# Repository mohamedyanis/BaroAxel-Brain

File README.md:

# BaroAxel Brain

This Printed Circuit Board (PCB) is based on the STM32 microcontroller as well as MEMS sensors (MPU6050 and BMP280).
The PCB is designed using the free and open source software <a href="https://github.com/KiCad">KiCad</a>. 

## More Details
BaroAxel Brain is a compact Printed Circuit Board (PCB) designed for industrial instrumentation applications. It integrates the STM32L0 series microcontroller, MPU6050 accelerometer, and BMP280 barometer, providing a comprehensive solution for asynchronous motor anomaly detection and other MEMS-based applications.

This board operates with a wide input voltage range from 4.75V to 12V, ensuring compatibility with various power sources commonly found in industrial environments. It features multiple connectors for UART communication, analog-to-digital conversion, and timer functions, offering flexibility for interfacing with diverse sensors and peripherals.

The STM32L0 MCU, renowned for its low-power operation and high-performance computing capabilities, drives the board's functionality. The integrated MPU6050 accelerometer enables precise measurement of acceleration, essential for monitoring vibrations and detecting anomalies in industrial machinery. Additionally, the BMP280 barometer facilitates accurate measurement of atmospheric pressure, enabling environmental monitoring in diverse industrial settings.

The compact design of BaroAxel Brain optimizes space utilization, making it suitable for integration into space-constrained industrial systems while maximizing functionality. It also includes an SWD connector for firmware updates, ensuring easy maintenance and scalability of the board.

This combination of features makes BaroAxel Brain an ideal choice for applications requiring robust industrial instrumentation, such as asynchronous motor anomaly detection and drone instrumentation, among others.

This board is designed back to 2021, ordered in 2023, and hand soldered in April 2024<br><br>

## Features :dart:
* [x] Four layers PCB
* [x] Low power
* [x] Small size (50x50mm)
* [x] Very easy to use

## Thank _You_!
Please :star: this repo to help us improve the quality.
<br><br>

## PCB Block Diagram
PCB System Block
:---------------------:

## 3D Viewer
Front View           | Back View
:---------------------:|:------------------:
 | 
Side View 1         |  Side View 2
 | 
Side View 3         |  Side View 4
 | 

## Before, During and After Soldering
Before 1            | Before 2
:---------------------:|:------------------:
 | 
During 1         |  During 2
 | 
After 1         |  After 2
 | 

## Testing the Functionality
Here I tested the functionality of the board after assembling it. I tested the built-in LEDs and the IMU (MPU6050) using I2C protocol, and print some texts on the laptop's screen using putty application via the UART-TTL converter.<br><br>

## 3D Enclosure Design
Here is the 3D Enclosure I designed using SolidWorks. The design contains the top and bottom pieces as well as a small glass plate just to show the electronics inside. Of course assembled with SolidWorks Assembly.
See the folder [3D](3D) in order to get the designs and print the parts using a 3D Printer.<br><br>
Enclosure Top           | Enclosure Bottom
:---------------------:|:------------------:
 | 
Enclosure Side 1         |  Enclosure Side 2
 | 

## Requirements

If you want to review the PCB or yoou wanna edit the schematics/layout, yoou only need to install KiCad software to your machine.

* Go to the <a href="https://www.kicad.org/download/">Official KiCad Download Page</a>.
* Select your operating system.
* Download the executable file and install it.

## Documentations
Open the [Datasheets](Datasheets) folder and you will find all the datasheets, applications notes, and design guidelines that help you understand the design better.

## How To Use It

1. Install this repository, click <a href="https://github.com/mohamedyanis/BaroAxel-Brain/archive/master.zip"> here </a> to install it. Or use git command:
```bach
git clone https://github.com/mohamedyanis/BaroAxel-Brain.git
```
3. Extract the folder and open it.
4. Navigate for the [Manufacturing](Manufacturing) folder.
5. Go to your best PCB manufacturer website and click on quote.
6. Upload the [BaroAxel_Brain_Gerber.rar](Manufacturing/Gerber/BaroAxel_Brain_Gerber.zip) in order to order the board.

## License
The content of this project is licenced under the [BSD 3-Clause "New" or "Revised" License](LICENSE).

## Contributing 💡
If you want to contribute to this project and make it better with new ideas, your pull request is very welcomed.<br>
If you find any issue just put it in the repository issue section, thanks!<br><br>
.سبحَانَكَ اللَّهُمَّ وَبِحَمْدِكَ، أَشْهَدُ أَنْ لا إِلهَ إِلأَ انْتَ أَسْتَغْفِرُكَ وَأَتْوبُ إِلَيْكَ

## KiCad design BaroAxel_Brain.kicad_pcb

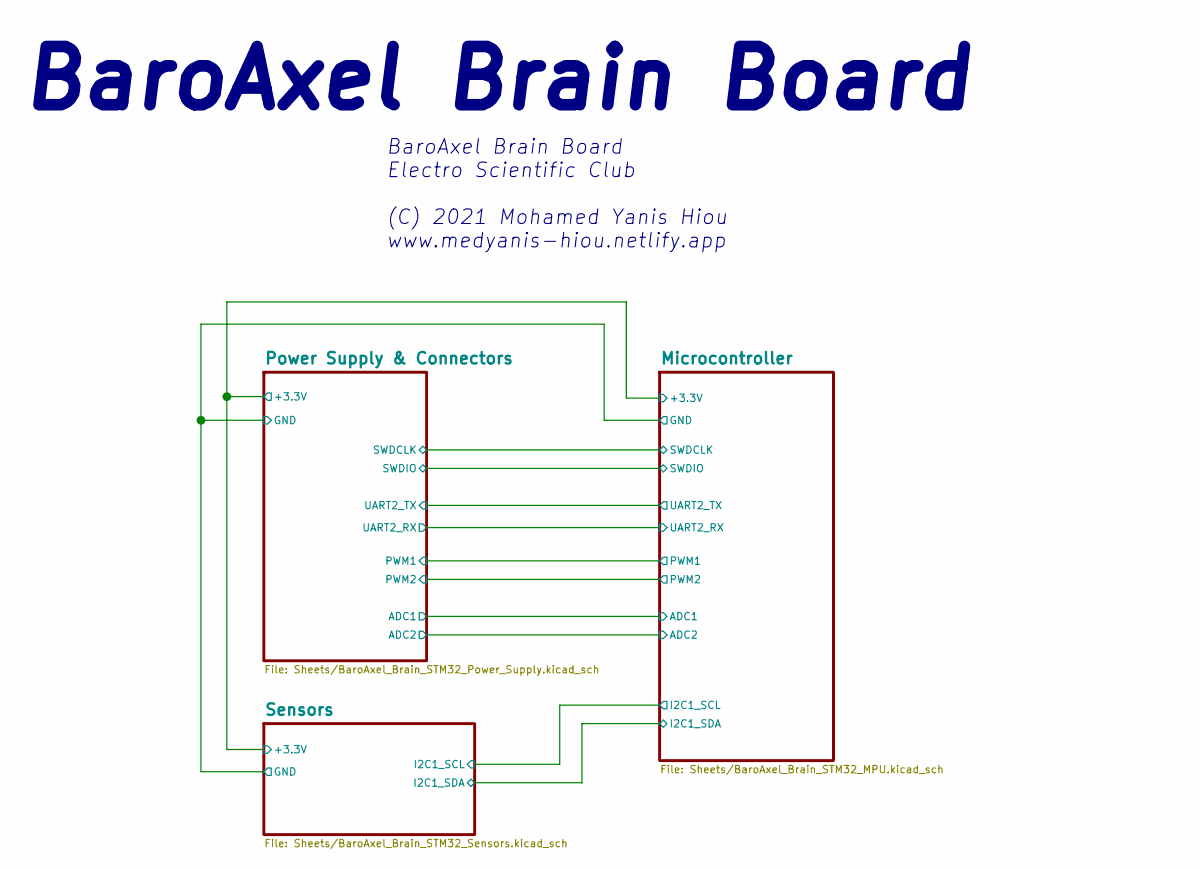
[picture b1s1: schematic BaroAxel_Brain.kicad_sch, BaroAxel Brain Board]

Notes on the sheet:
BaroAxel Brain Board Electro Scientific Club (C) 2021 Mohamed Yanis Hiou www.medyanis-hiou.netlify.app
BaroAxel Brain Board

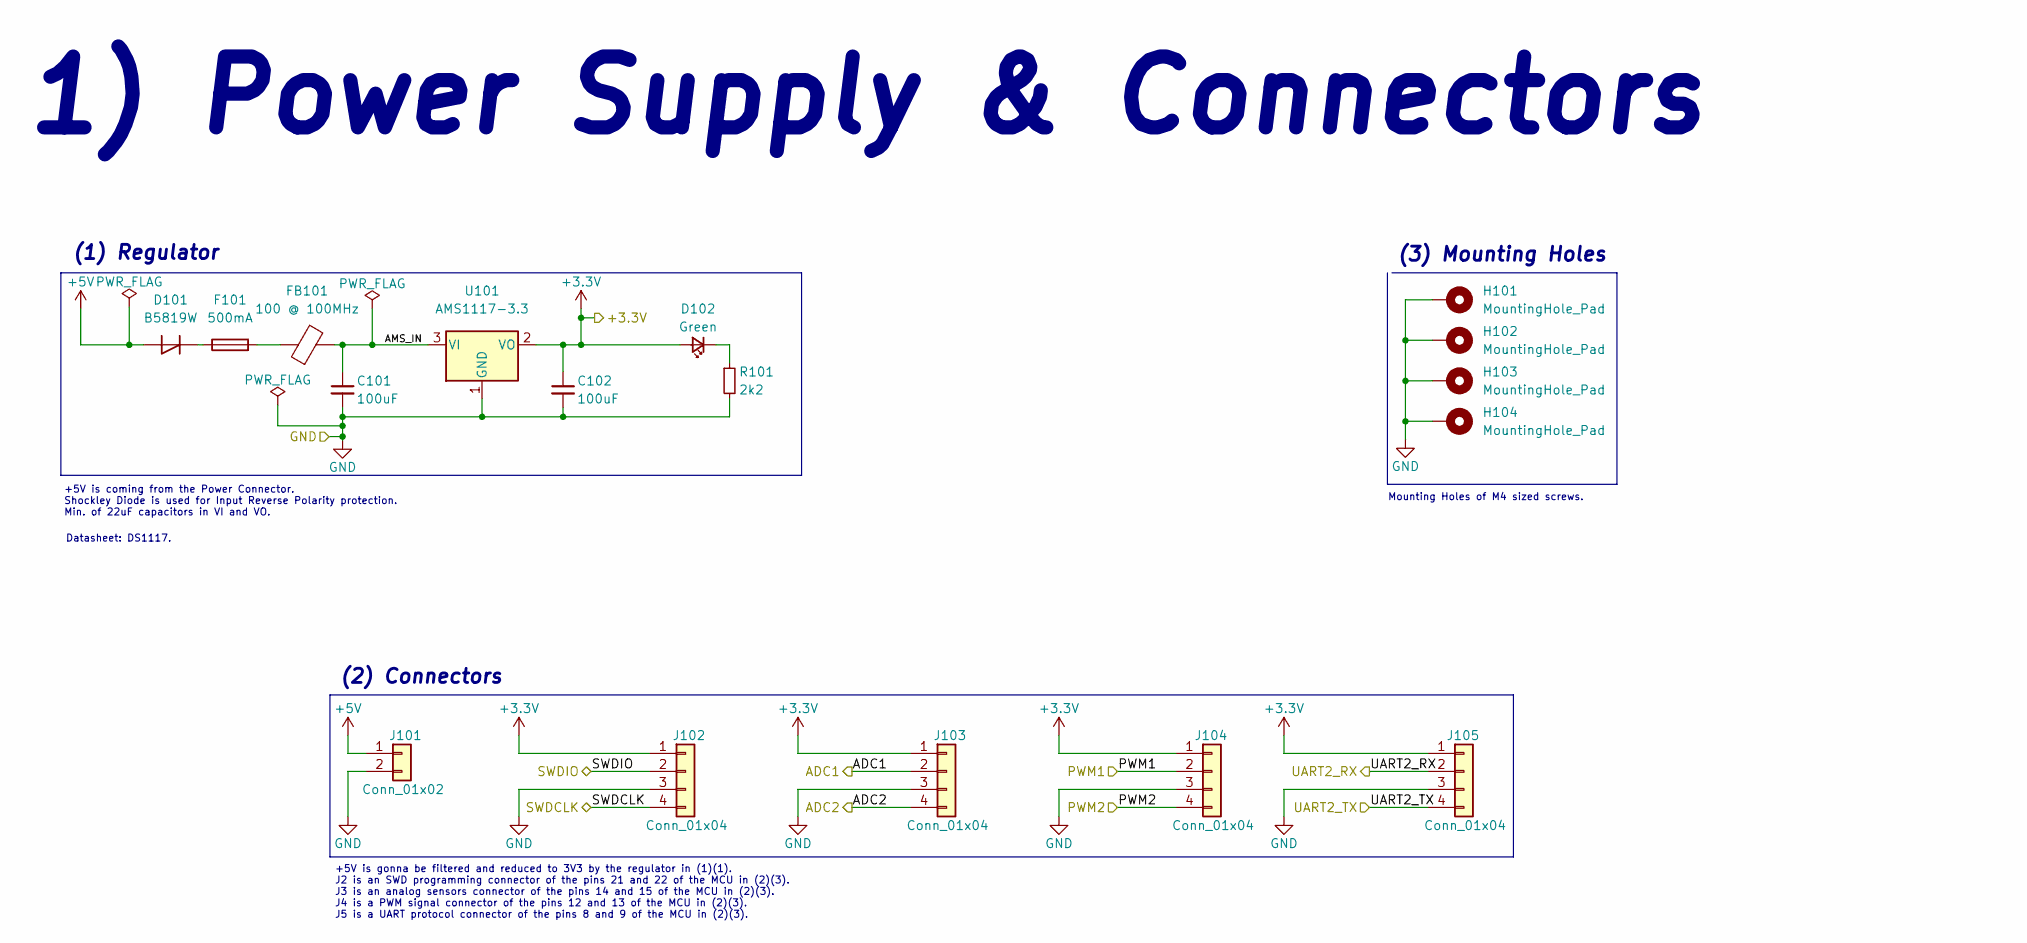
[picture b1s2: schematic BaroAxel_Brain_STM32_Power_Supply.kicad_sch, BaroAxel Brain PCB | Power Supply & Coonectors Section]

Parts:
C101, C102: 100uF; C_0603_1608Metric
D101: B5819W; D_1206_3216Metric
D102: Green; LED_0603_1608Metric
F101: 500mA; Fuse_0805_2012Metric
FB101: 100 @ 100MHz; L_0603_1608Metric
H101, H102, H103, H104: MountingHole_Pad; MountingHole_4.3mm_M4_Pad_Via
J101: Conn_01x02; JST_XH_S2B-XH-A_1x02_P2.50mm_Horizontal
J102, J103, J104, J105: Conn_01x04; JST_XH_S4B-XH-A_1x04_P2.50mm_Horizontal
R101: 2k2; R_0402_1005Metric
U101: AMS1117-3.3; SOT-223-3_TabPin2

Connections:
+5V: D101.2 (A), J101.1
/Microcontroller/ADC1: J103.2; also elsewhere on the board
/Microcontroller/ADC2: J103.4; also elsewhere on the board
/Microcontroller/PWM1: J104.2; also elsewhere on the board
/Microcontroller/PWM2: J104.4; also elsewhere on the board
/Microcontroller/SWDCLK: J102.4; also elsewhere on the board
/Microcontroller/SWDIO: J102.2; also elsewhere on the board
/Microcontroller/UART2_RX: J105.2; also elsewhere on the board
/Microcontroller/UART2_TX: J105.4; also elsewhere on the board
/Power Supply & Connectors/AMS_IN: C101.1, FB101.2, U101.3 (VI)
unnamed: D101.1 (K), F101.1
unnamed: D102.1 (K), R101.1
unnamed: F101.2, FB101.1

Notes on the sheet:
+5V is coming from the Power Connector. Shockley Diode is used for Input Reverse Polarity protection. Min. of 22uF capacitors in VI and VO.
1) Power Supply & Connectors
Datasheet: DS1117.
(3) Mounting Holes
Mounting Holes of M4 sized screws.
+5V is gonna be filtered and reduced to 3V3 by the regulator in (1)(1). J2 is an SWD programming connector of the pins 21 and 22 of the MCU in (2)(3). J3 is an analog sensors connector of the pins 14 and 15 of the MCU in (2)(3). J4 is a PWM signal connector of the pins 12 and 13 of the MCU in (2)(3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
(1) Regulator
(2) Connectors

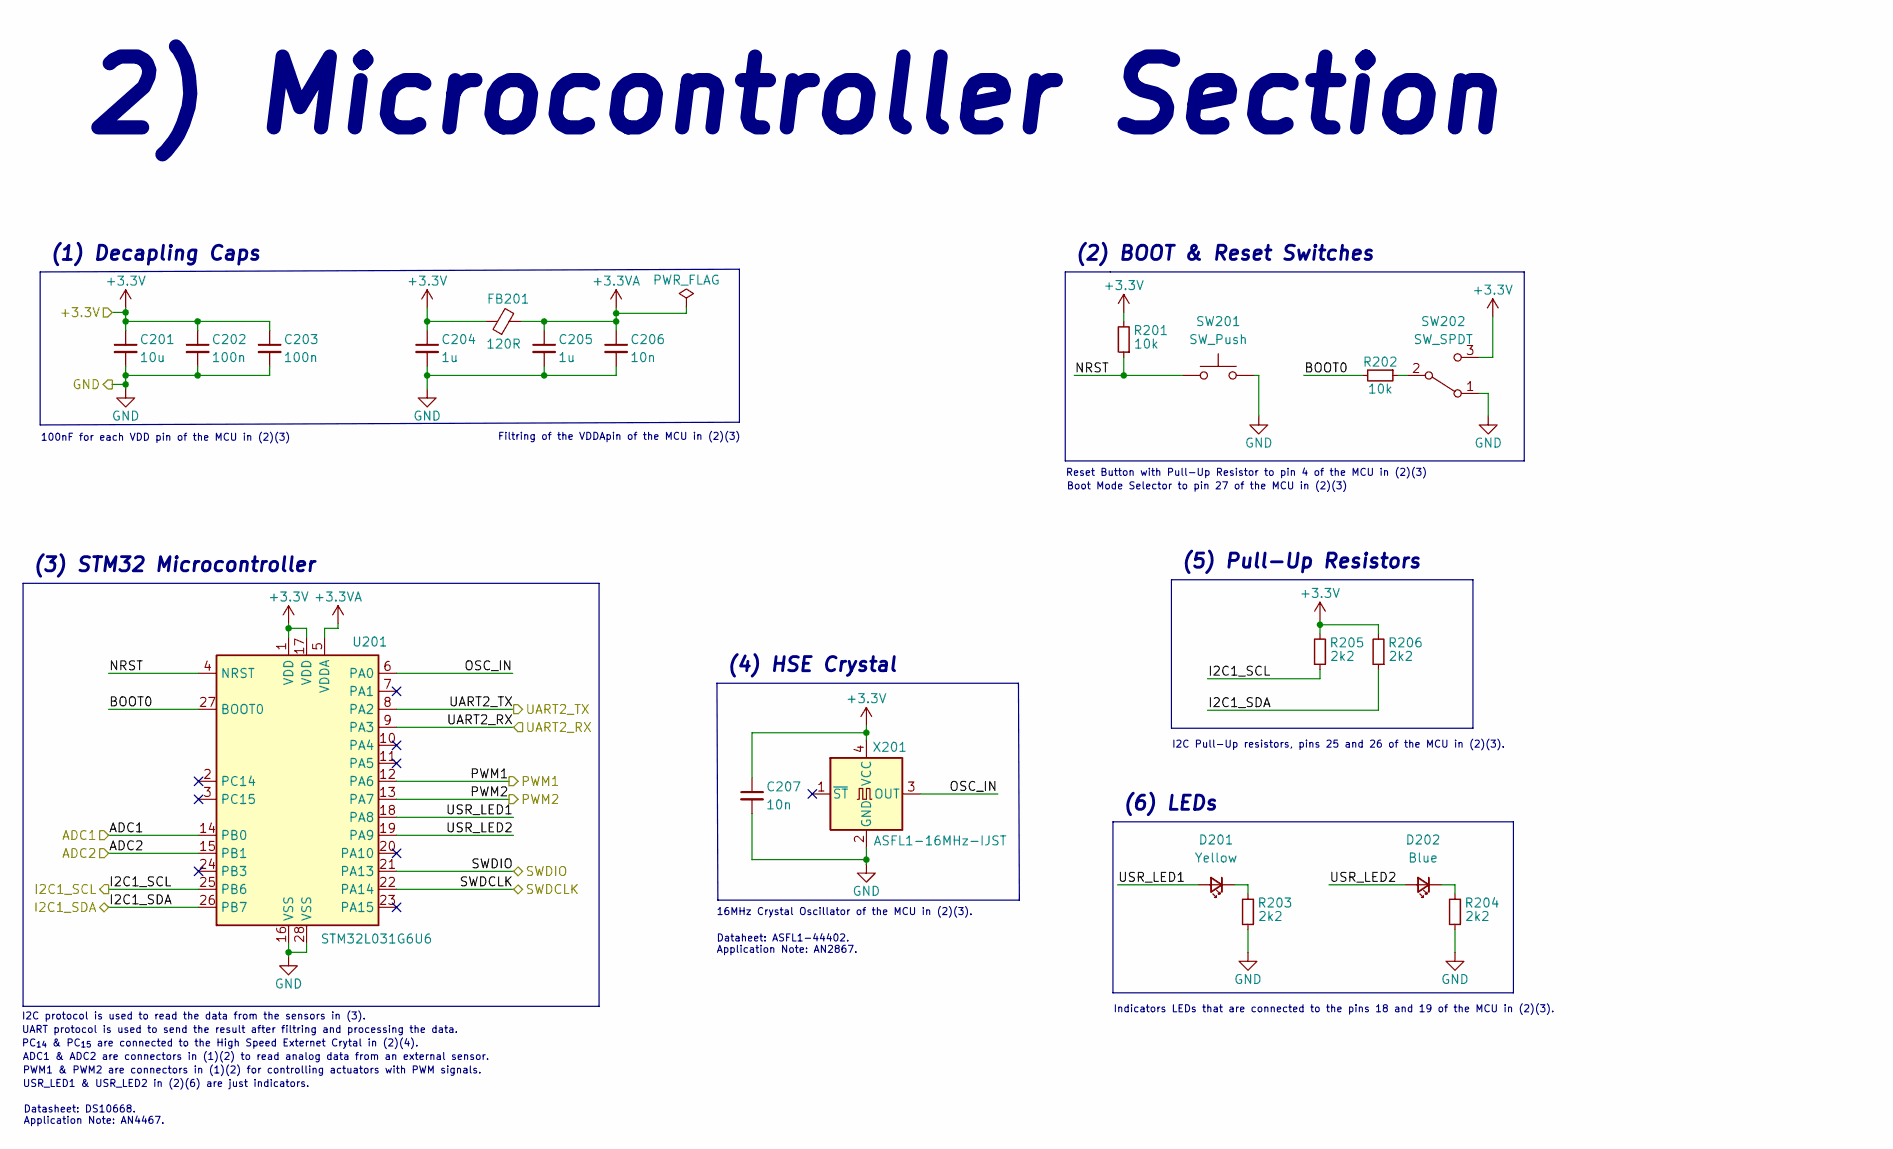
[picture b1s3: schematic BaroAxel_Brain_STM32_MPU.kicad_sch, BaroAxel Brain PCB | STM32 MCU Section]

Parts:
C201: 10u; C_0402_1005Metric
C202, C203: 100n; C_0402_1005Metric
C204, C205: 1u; C_0402_1005Metric
C206, C207: 10n; C_0402_1005Metric
D201: Yellow; LED_0603_1608Metric
D202: Blue; LED_0603_1608Metric
FB201: 120R; L_0603_1608Metric
R201, R202: 10k; R_0402_1005Metric
R203, R204, R205, R206: 2k2; R_0402_1005Metric
SW201: SW_Push; SW_SPST_B3U-1000P-B
SW202: SW_SPDT; SW_SPDT_PCM12
U201: STM32L031G6U6; QFN-28_4x4mm_P0.5mm
X201: ASFL1-16MHz-IJST; Oscillator_SMD_SeikoEpson_SG8002LB-4Pin_5.0x3.2mm

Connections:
+3.3VA: C205.1, C206.1, FB201.2, U201.5 (VDDA)
/Microcontroller/ADC1: U201.14 (PB0); also elsewhere on the board
/Microcontroller/ADC2: U201.15 (PB1); also elsewhere on the board
/Microcontroller/BOOT0: R202.2, U201.27 (BOOT0)
/Microcontroller/I2C1_SCL: R205.1, U201.25 (PB6); also elsewhere on the board
/Microcontroller/I2C1_SDA: R206.1, U201.26 (PB7); also elsewhere on the board
/Microcontroller/NRST: R201.1, SW201.1, U201.4 (NRST)
/Microcontroller/OSC_IN: U201.6 (PA0), X201.3 (OUT)
/Microcontroller/PWM1: U201.12 (PA6); also elsewhere on the board
/Microcontroller/PWM2: U201.13 (PA7); also elsewhere on the board
/Microcontroller/SWDCLK: U201.22 (PA14); also elsewhere on the board
/Microcontroller/SWDIO: U201.21 (PA13); also elsewhere on the board
/Microcontroller/UART2_RX: U201.9 (PA3); also elsewhere on the board
/Microcontroller/UART2_TX: U201.8 (PA2); also elsewhere on the board
/Microcontroller/USR_LED1: D201.2 (A), U201.18 (PA8)
/Microcontroller/USR_LED2: D202.2 (A), U201.19 (PA9)
unnamed: D201.1 (K), R203.2
unnamed: D202.1 (K), R204.2
unnamed: R202.1, SW202.2 (B)

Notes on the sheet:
I2C Pull-Up resistors, pins 25 and 26 of the MCU in (2)(3).
16MHz Crystal Oscillator of the MCU in (2)(3).
Boot Mode Selector to pin 27 of the MCU in (2)(3)
2) Microcontroller Section
USR_LED1 & USR_LED2 in (2)(6) are just indicators.
Datasheet: DS10668. Application Note: AN4467.
(4) HSE Crystal
UART protocol is used to send the result after filtring and processing the data.
100nF for each VDD pin of the MCU in (2)(3)
(1) Decapling Caps
ADC1 & ADC2 are connectors in (1)(2) to read analog data from an external sensor.
(5) Pull-Up Resistors
Indicators LEDs that are connected to the pins 18 and 19 of the MCU in (2)(3).
(6) LEDs
(2) BOOT & Reset Switches
PC_{14} & PC_{15} are connected to the High Speed Externet Crytal in (2)(4).
PWM1 & PWM2 are connectors in (1)(2) for controlling actuators with PWM signals.
(3) STM32 Microcontroller
I2C protocol is used to read the data from the sensors in (3).
Filtring of the VDDApin of the MCU in (2)(3)
Dataheet: ASFL1-44402. Application Note: AN2867.
Reset Button with Pull-Up Resistor to pin 4 of the MCU in (2)(3)

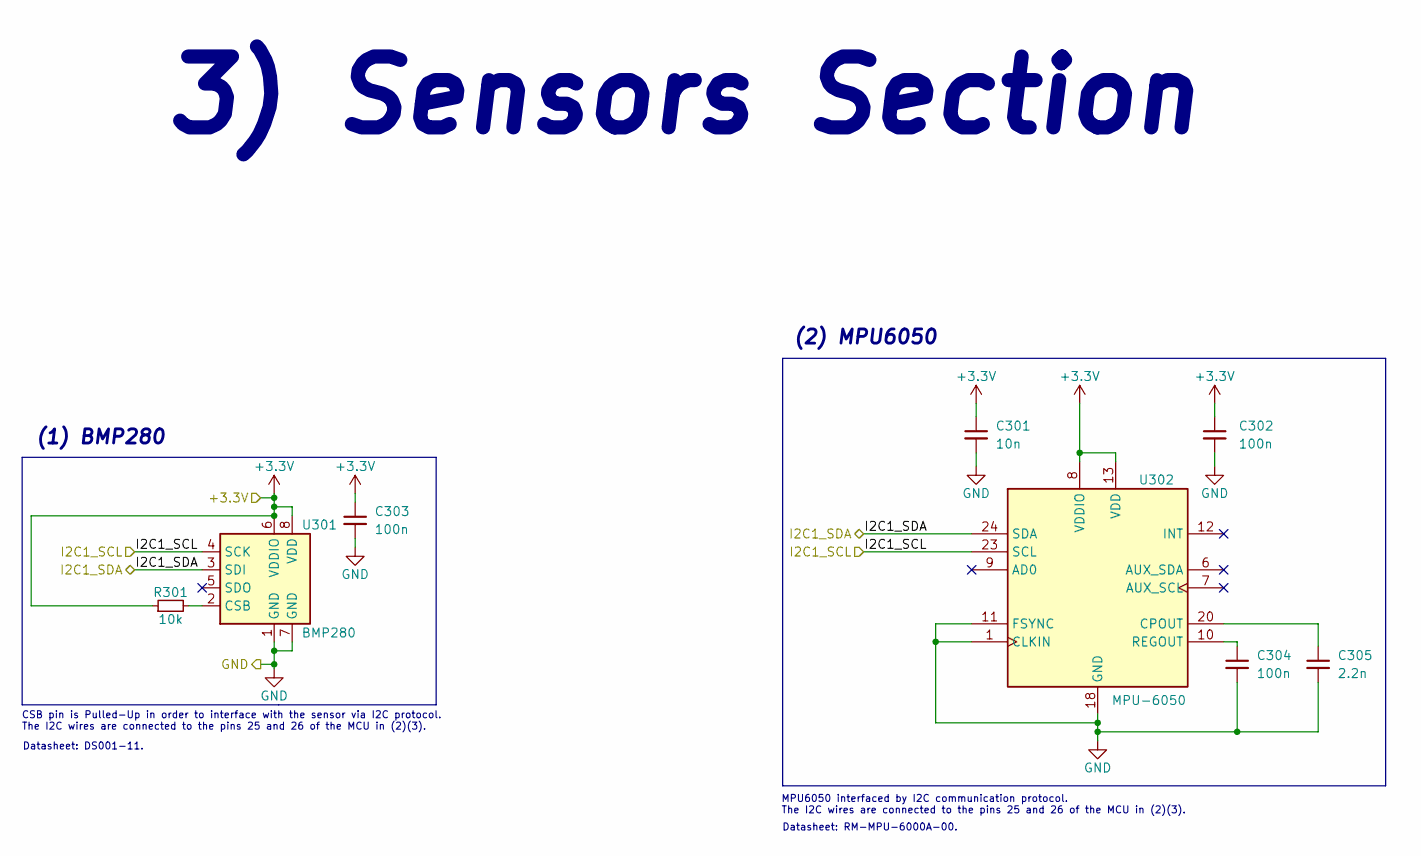
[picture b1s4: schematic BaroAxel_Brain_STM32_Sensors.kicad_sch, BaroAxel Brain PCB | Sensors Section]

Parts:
C301: 10n; C_0402_1005Metric
C302, C303, C304: 100n; C_0402_1005Metric
C305: 2.2n; C_0402_1005Metric
R301: 10k; R_0402_1005Metric
U301: BMP280; Bosch_LGA-8_2x2.5mm_P0.65mm_ClockwisePinNumbering
U302: MPU-6050; InvenSense_QFN-24_4x4mm_P0.5mm

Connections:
/Microcontroller/I2C1_SCL: U301.4 (SCK), U302.23 (SCL); also elsewhere on the board
/Microcontroller/I2C1_SDA: U301.3 (SDI), U302.24 (SDA); also elsewhere on the board
unnamed: C304.1, U302.10 (REGOUT)
unnamed: C305.1, U302.20 (CPOUT)
unnamed: R301.2, U301.2 (CSB)

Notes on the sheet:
MPU6050 interfaced by I2C communication protocol. The I2C wires are connected to the pins 25 and 26 of the MCU in (2)(3).
Datasheet: RM-MPU-6000A-00.
3) Sensors Section
(2) MPU6050
Datasheet: DS001-11.
CSB pin is Pulled-Up in order to interface with the sensor via I2C protocol. The I2C wires are connected to the pins 25 and 26 of the MCU in (2)(3).
(1) BMP280

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
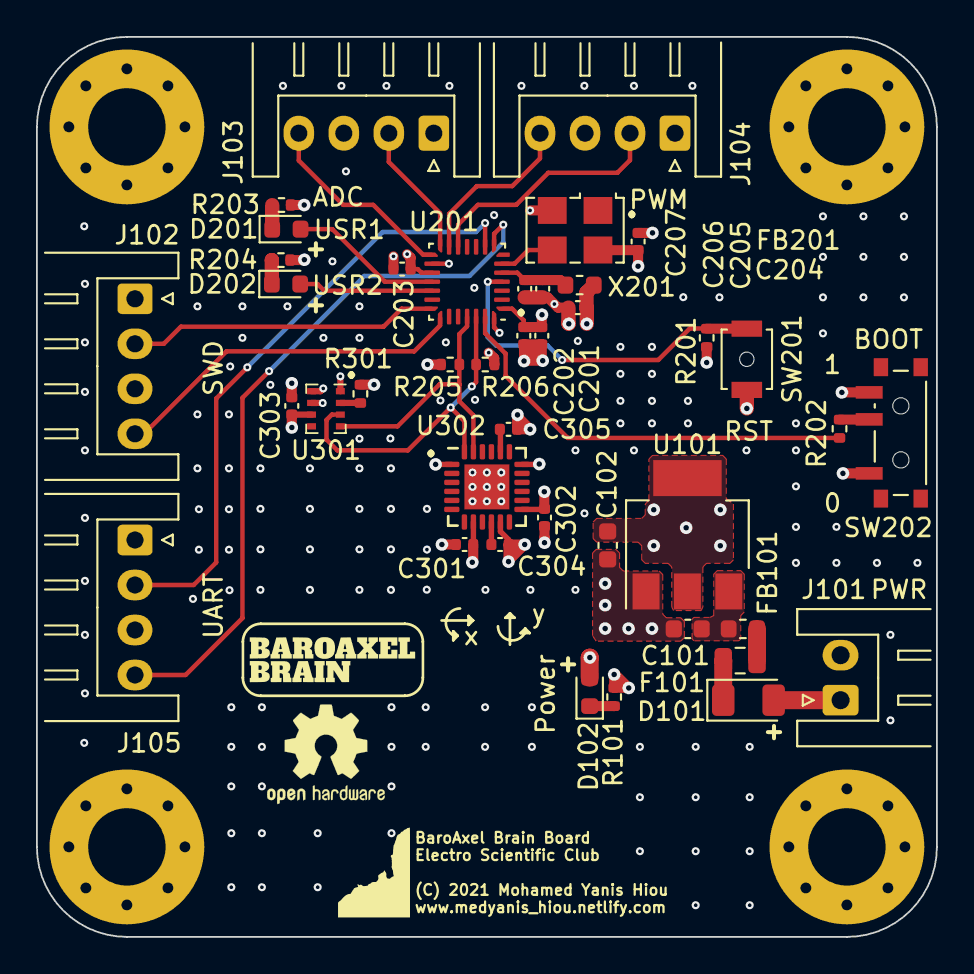
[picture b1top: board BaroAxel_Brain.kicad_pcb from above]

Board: 4 copper layers, 50.0 x 50.0 mm, 45 parts (0 on the bottom side), 29 nets.

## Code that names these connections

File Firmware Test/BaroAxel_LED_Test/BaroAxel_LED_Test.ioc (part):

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Mcu.Name=STM32L031G(4-6)Ux
Mcu.Package=UFQFPN28
Mcu.UserName=STM32L031G6Ux
PA0-CK_IN.Mode=HSE-External-Clock-Source-for-LittleNemo
PA0-CK_IN.Signal=RCC_CK_IN
PA10.Mode=I2C
PA10.Signal=I2C1_SDA
PA13.Mode=Serial_Wire
PA13.Signal=SYS_SWDIO
PA14.Mode=Serial_Wire
PA14.Signal=SYS_SWCLK
PA2.Mode=Asynchronous
PA2.Signal=USART2_TX
PA3.Mode=Asynchronous
PA3.Signal=USART2_RX
PA8.GPIOParameters=GPIO_Label
PA8.GPIO_Label=LED1
PA8.Signal=GPIO_Output
PA9.GPIOParameters=GPIO_Label
PA9.GPIO_Label=LED2
PA9.Signal=GPIO_Output
PB6.Mode=I2C
PB6.Signal=I2C1_SCL
RCC.HSE_VALUE=16000000
RCC.SYSCLKFreq_VALUE=24000000
RCC.SYSCLKSource=RCC_SYSCLKSOURCE_PLLCLK
board=custom

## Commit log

2024-05-01 Initial Commit Upload
2024-05-01 Updating README
2024-06-12 Modifying the Gerber File

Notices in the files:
README.md:
License: BSD 3-Clause
